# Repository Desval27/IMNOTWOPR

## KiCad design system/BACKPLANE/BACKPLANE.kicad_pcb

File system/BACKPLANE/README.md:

# BACKPLANE

System Bus

Status: Untested

The BACKPLANE PCB provides the shared bus and power distribution for the IMNOTWOPR modular computer, connecting CPU, memory, I/O, and front-panel cards through 20 96-pin DIN 41612 slots. It carries the 24-bit address bus, 8-bit data bus, clock and control signals, and auxiliary I²C and SPI interfaces. ATX power connectors supply the system power rails, with standby power and power-control signals available to the cards. ~~The passive design also includes jumper-selectable I²C pull-ups.~~

~~The PWR module and the BACKPLANE both provide the option for I²C pull-ups for convenience.  Only on should be enabled at a time.~~

Optional I²C pullups will ultimately be provided by the [bus terminator card](../../modules/XXX/README.md).  Support is retained here for testing/hacking purposes and may be removed in a later revision.

## Documents

- [Schematic](BACKPLANE_schematic.pdf)
- [Assembly](BACKPLANE_assembly.pdf)
- [Bill of Materials](bom.csv)
- [Interactive Bill of Materials](ibom.html)

## Gerber To Order

- [Default](gerber_to_order/BACKPLANE_425.28x128.7mm_for_Default.zip)
- [Elecrow](gerber_to_order/BACKPLANE_425.28x128.7mm_for_Elecrow.zip)
- [FusionPCB](gerber_to_order/BACKPLANE_425.28x128.7mm_for_FusionPCB.zip)
- [JLCPCB](gerber_to_order/BACKPLANE_425.28x128.7mm_for_JLCPCB.zip)
- [PCBWay](gerber_to_order/BACKPLANE_425.28x128.7mm_for_PCBWay.zip)

## Rendered Images

### Top 3D

 3D

### Top

### Bottom

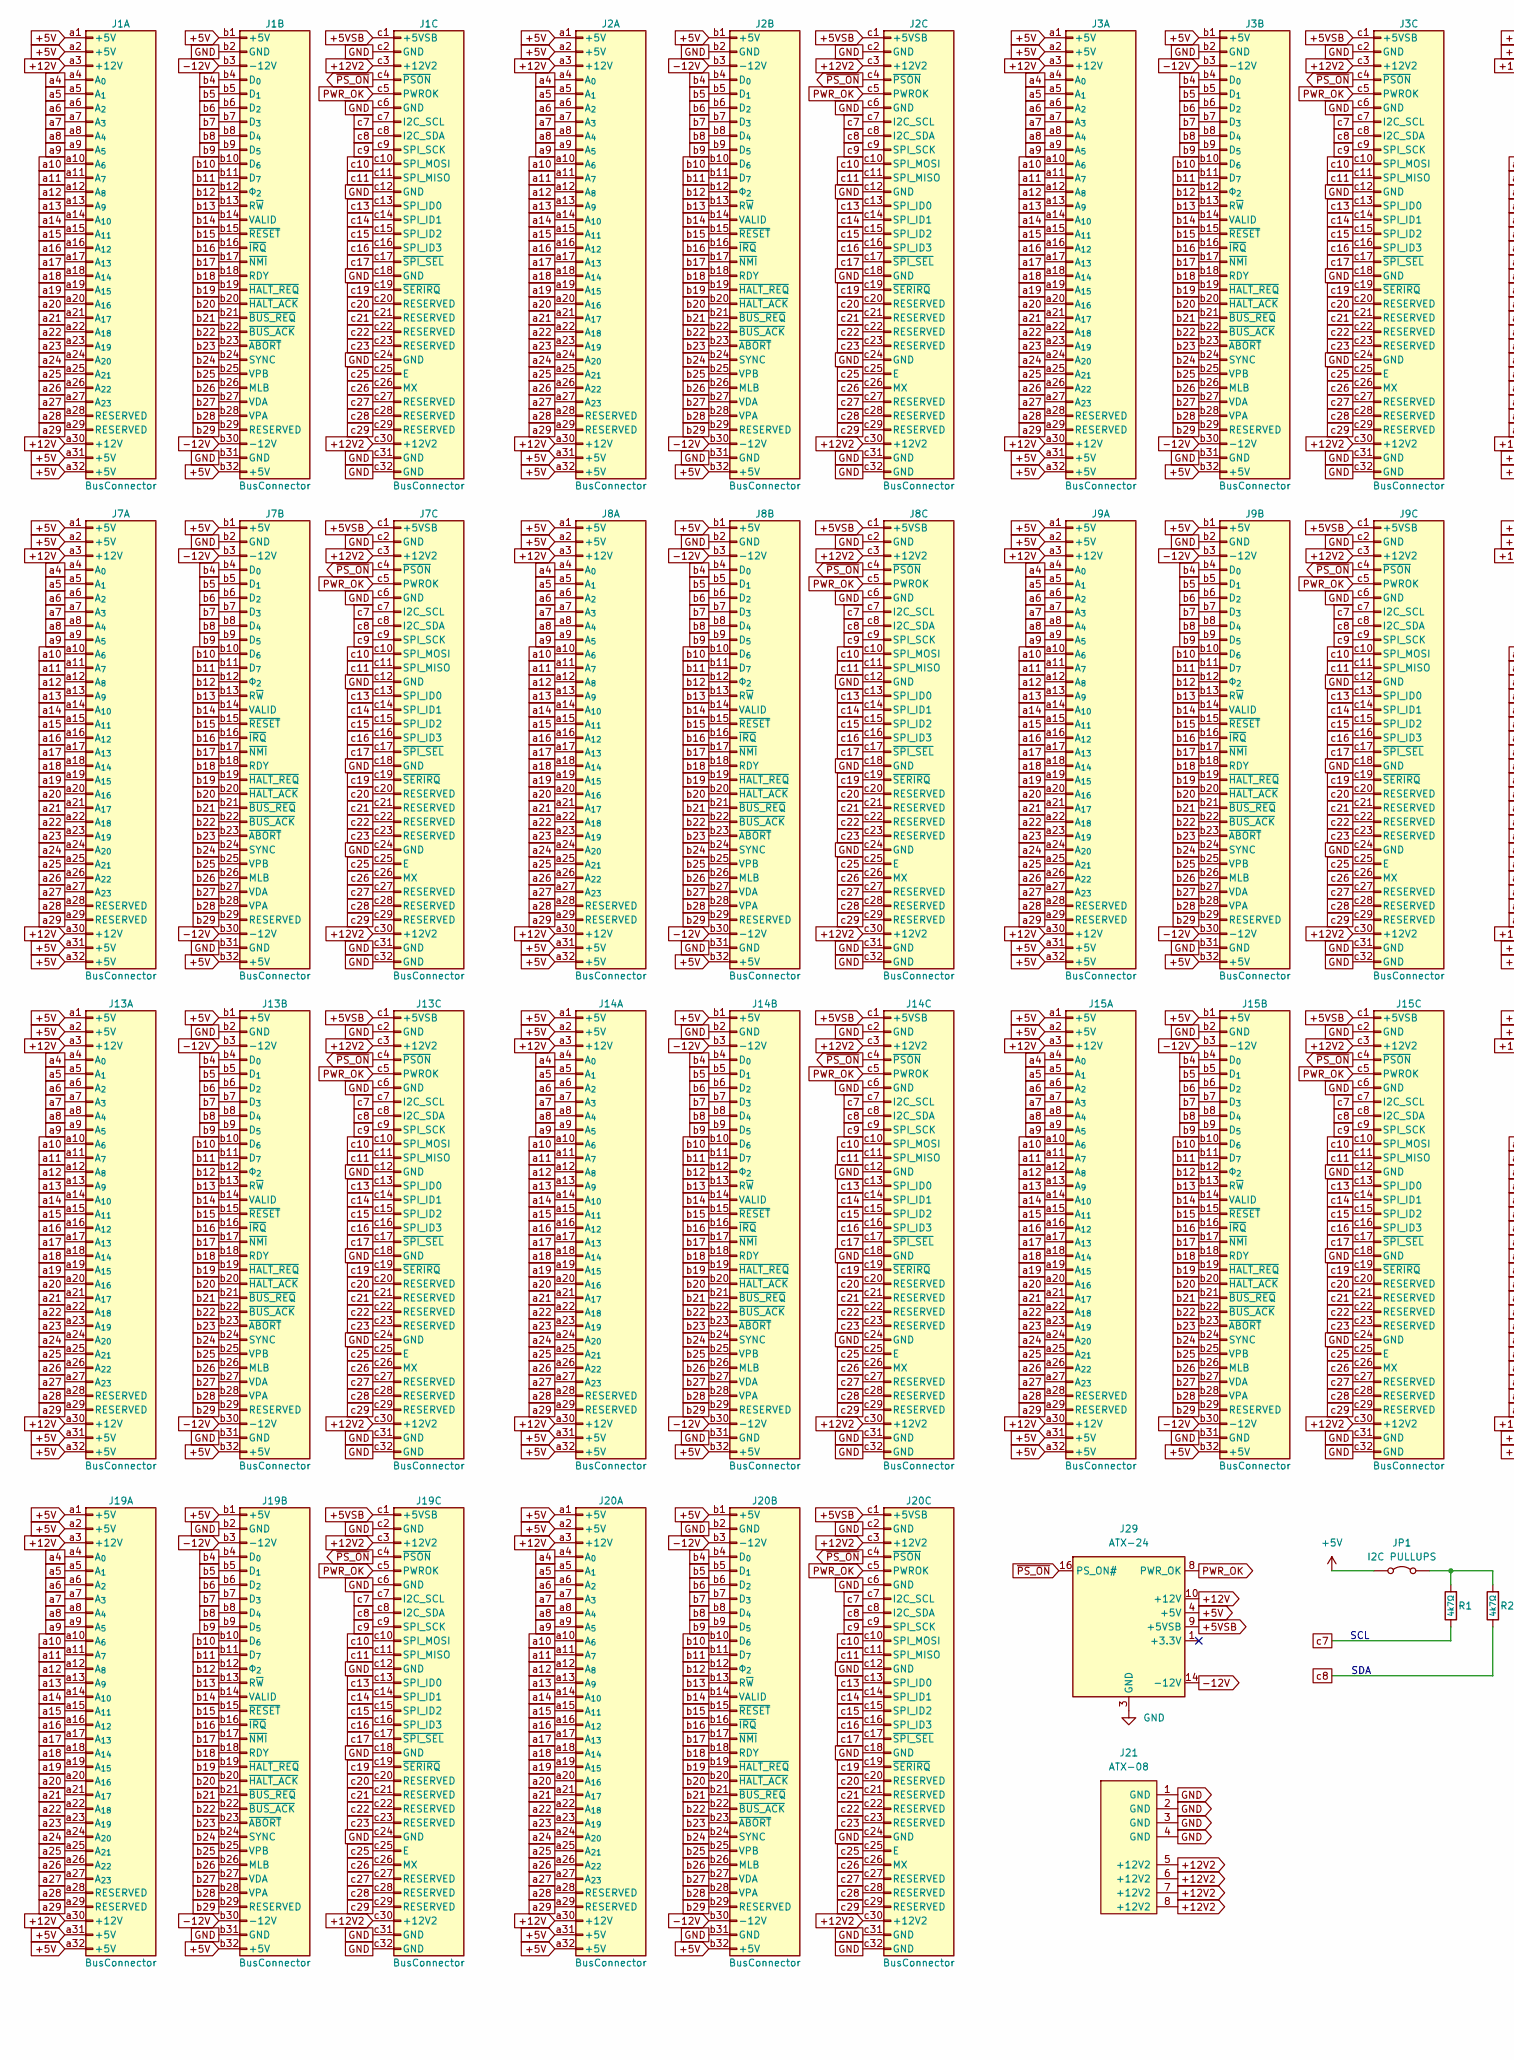
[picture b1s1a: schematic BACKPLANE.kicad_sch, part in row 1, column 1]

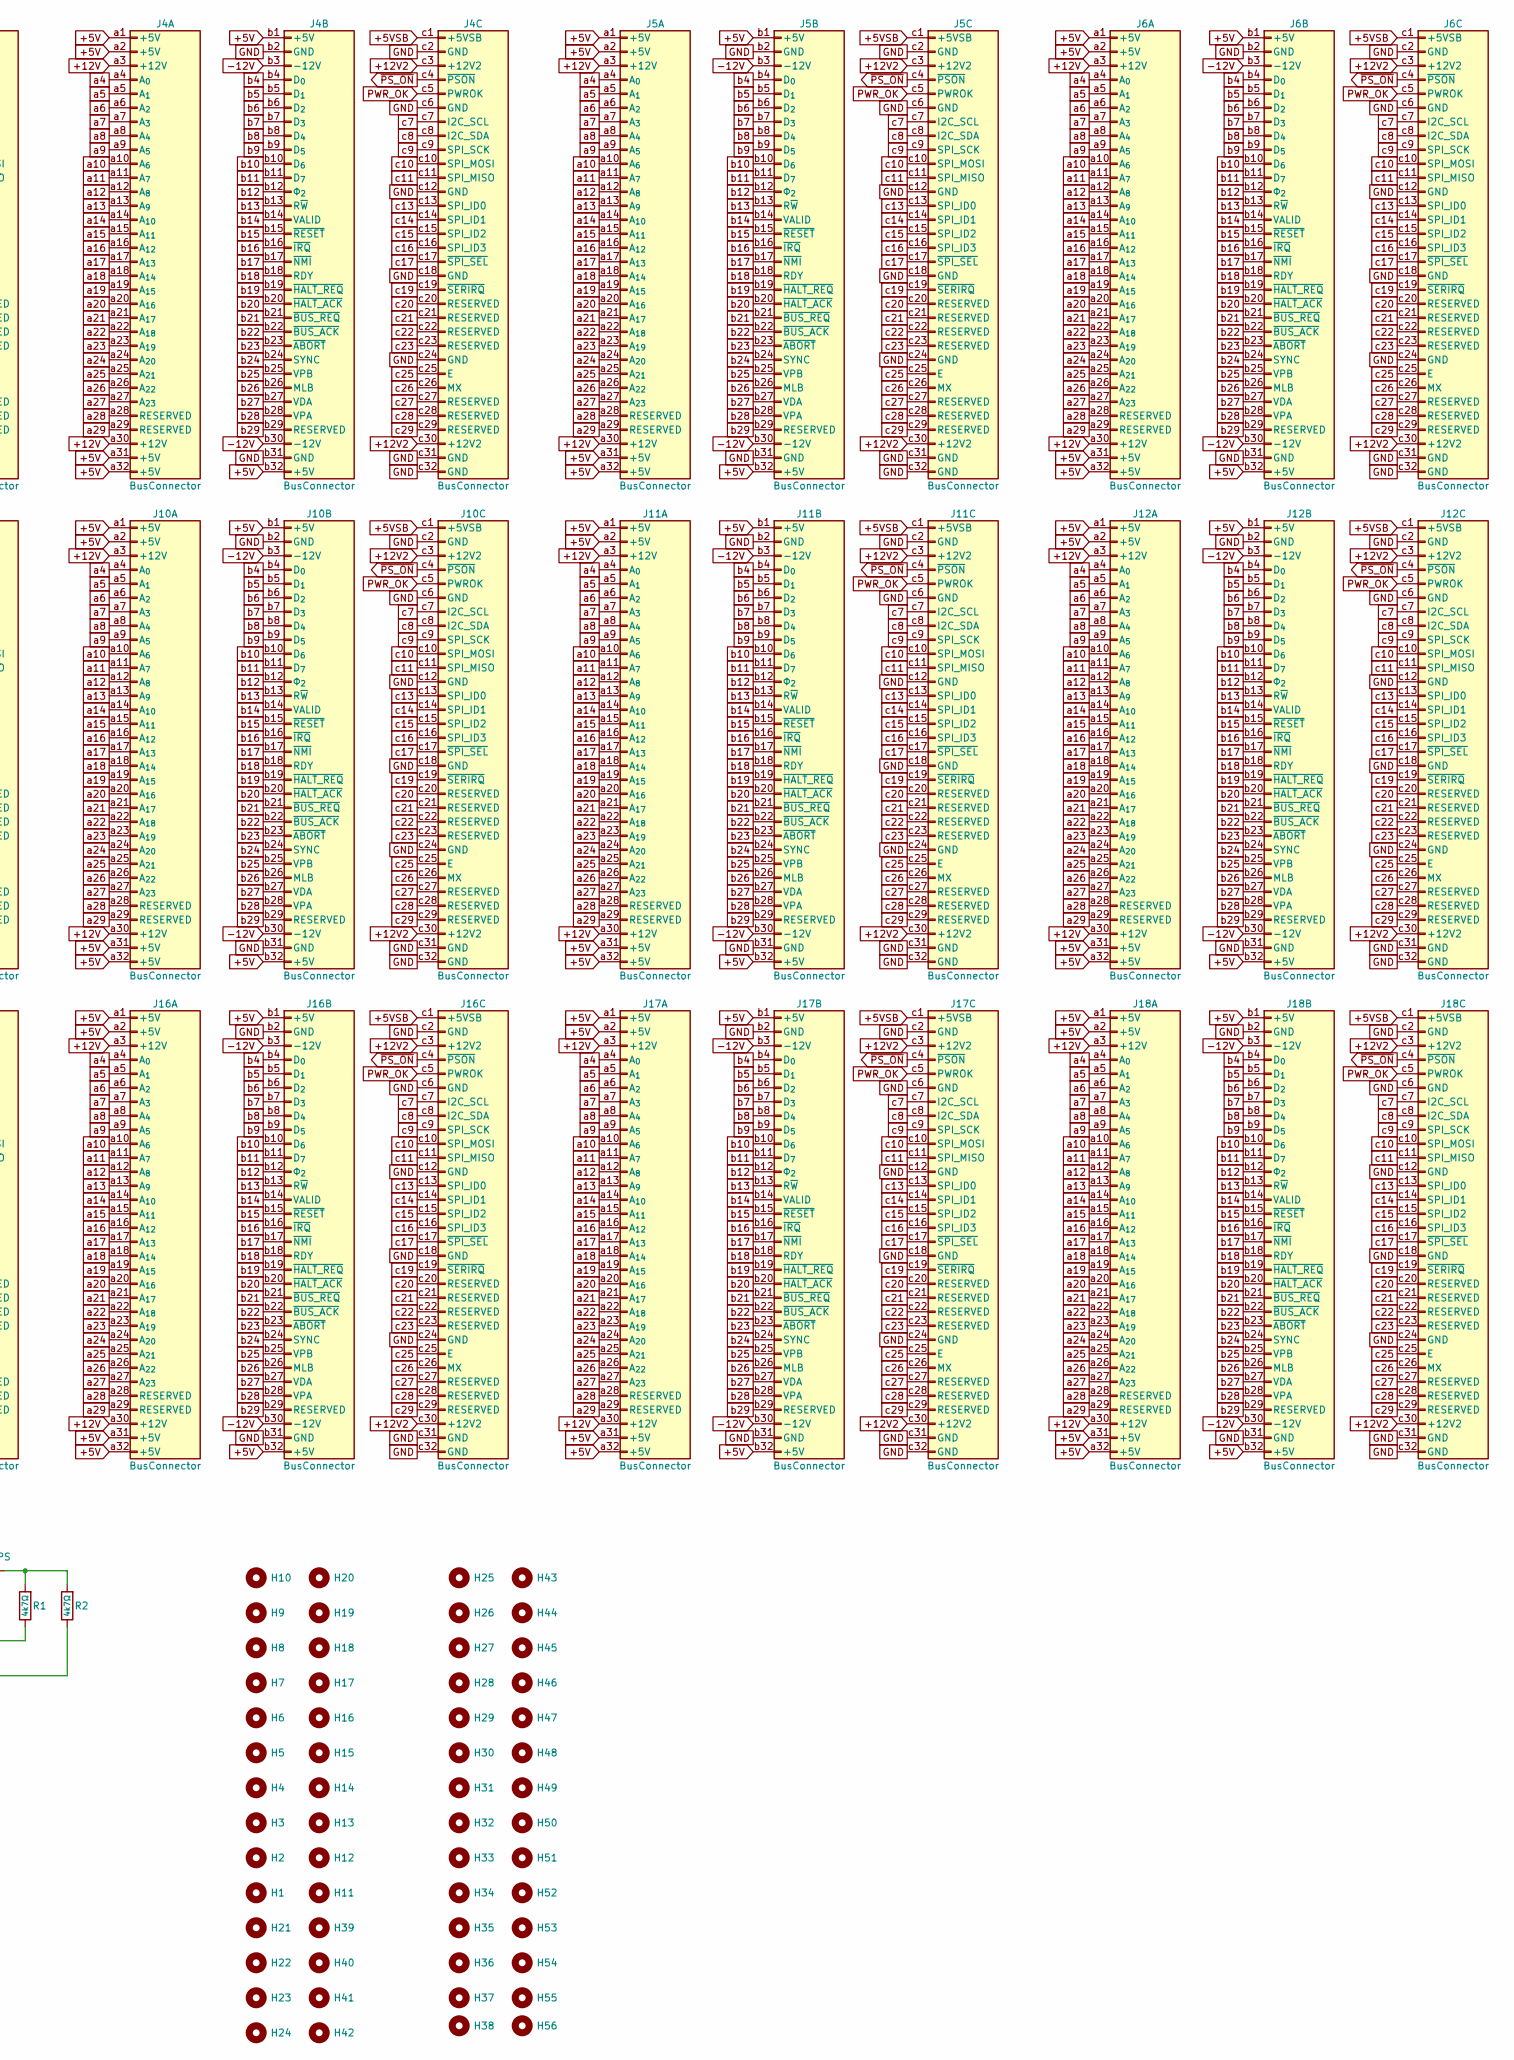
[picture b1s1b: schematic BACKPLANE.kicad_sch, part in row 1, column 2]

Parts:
H1, H2, H3, H4, H5, H6, H7, H8, H9, H10, H11, H12, H13, H14, H15, H16, H17, H18, H19, H20, H21, H22, H23, H24, H25, H26, H27, H28, H29, H30, H31, H32, H33, H34, H35, H36, H37, H38, H39, H40, H41, H42, H43, H44, H45, H46, H47, H48, H49, H50, H51, H52, H53, H54, H55, H56: MountingHole; MountingHole_2.7mm_M2.5
J1, J2, J3, J4, J5, J6, J7, J8, J9, J10, J11, J12, J13, J14, J15, J16, J17, J18, J19, J20: BusConnector; SystemConnector_Female
J21: ATX-08
J29: ATX-24
JP1: I2C PULLUPS; Jumper_1x02
R1, R2: 4k7Ω; R_Axial_DIN0207_P400mil

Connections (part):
+5V: J1.a1 (+5V), J1.a2 (+5V), J1.a31 (+5V), J1.a32 (+5V), J1.b1 (+5V), J1.b32 (+5V), J2.a1 (+5V), J2.a2 (+5V), J2.a31 (+5V), J2.a32 (+5V), J2.b1 (+5V), J2.b32 (+5V), J3.a1 (+5V), J3.a2 (+5V), J3.a31 (+5V), J3.a32 (+5V), J3.b1 (+5V), J3.b32 (+5V), J4.a1 (+5V), J4.a2 (+5V), J4.a31 (+5V), J4.a32 (+5V), J4.b1 (+5V), J4.b32 (+5V), J5.a1 (+5V), J5.a2 (+5V), J5.a31 (+5V), J5.a32 (+5V), J5.b1 (+5V), J5.b32 (+5V), J6.a1 (+5V), J6.a2 (+5V), J6.a31 (+5V), J6.a32 (+5V), J6.b1 (+5V), J6.b32 (+5V), J7.a1 (+5V), J7.a2 (+5V), J7.a31 (+5V), J7.a32 (+5V), J7.b1 (+5V), J7.b32 (+5V), J8.a1 (+5V), J8.a2 (+5V), J8.a31 (+5V), J8.a32 (+5V), J8.b1 (+5V), J8.b32 (+5V), J9.a1 (+5V), J9.a2 (+5V), J9.a31 (+5V), J9.a32 (+5V), J9.b1 (+5V), J9.b32 (+5V), J10.a1 (+5V), J10.a2 (+5V), J10.a31 (+5V), J10.a32 (+5V), J10.b1 (+5V), J10.b32 (+5V), J11.a1 (+5V), J11.a2 (+5V), J11.a31 (+5V), J11.a32 (+5V), J11.b1 (+5V), J11.b32 (+5V), J12.a1 (+5V), J12.a2 (+5V), J12.a31 (+5V), J12.a32 (+5V), J12.b1 (+5V), J12.b32 (+5V), J13.a1 (+5V), J13.a2 (+5V), J13.a31 (+5V), J13.a32 (+5V), J13.b1 (+5V), J13.b32 (+5V), J14.a1 (+5V), J14.a2 (+5V)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
+5VSB: J1.c1 (+5VSB), J2.c1 (+5VSB), J3.c1 (+5VSB), J4.c1 (+5VSB), J5.c1 (+5VSB), J6.c1 (+5VSB), J7.c1 (+5VSB), J8.c1 (+5VSB), J9.c1 (+5VSB), J10.c1 (+5VSB), J11.c1 (+5VSB), J12.c1 (+5VSB), J13.c1 (+5VSB), J14.c1 (+5VSB), J15.c1 (+5VSB), J16.c1 (+5VSB), J17.c1 (+5VSB), J18.c1 (+5VSB), J19.c1 (+5VSB), J20.c1 (+5VSB), J29.9 (+5VSB)
+12V: J1.a3 (+12V), J1.a30 (+12V), J2.a3 (+12V), J2.a30 (+12V), J3.a3 (+12V), J3.a30 (+12V), J4.a3 (+12V), J4.a30 (+12V), J5.a3 (+12V), J5.a30 (+12V), J6.a3 (+12V), J6.a30 (+12V), J7.a3 (+12V), J7.a30 (+12V), J8.a3 (+12V), J8.a30 (+12V), J9.a3 (+12V), J9.a30 (+12V), J10.a3 (+12V), J10.a30 (+12V), J11.a3 (+12V), J11.a30 (+12V), J12.a3 (+12V), J12.a30 (+12V), J13.a3 (+12V), J13.a30 (+12V), J14.a3 (+12V), J14.a30 (+12V), J15.a3 (+12V), J15.a30 (+12V), J16.a3 (+12V), J16.a30 (+12V), J17.a3 (+12V), J17.a30 (+12V), J18.a3 (+12V), J18.a30 (+12V), J19.a3 (+12V), J19.a30 (+12V), J20.a3 (+12V), J20.a30 (+12V), J29.10 (+12V), J29.11 (+12V)
+12V2: J1.c3 (+12V2), J1.c30 (+12V2), J2.c3 (+12V2), J2.c30 (+12V2), J3.c3 (+12V2), J3.c30 (+12V2), J4.c3 (+12V2), J4.c30 (+12V2), J5.c3 (+12V2), J5.c30 (+12V2), J6.c3 (+12V2), J6.c30 (+12V2), J7.c3 (+12V2), J7.c30 (+12V2), J8.c3 (+12V2), J8.c30 (+12V2), J9.c3 (+12V2), J9.c30 (+12V2), J10.c3 (+12V2), J10.c30 (+12V2), J11.c3 (+12V2), J11.c30 (+12V2), J12.c3 (+12V2), J12.c30 (+12V2), J13.c3 (+12V2), J13.c30 (+12V2), J14.c3 (+12V2), J14.c30 (+12V2), J15.c3 (+12V2), J15.c30 (+12V2), J16.c3 (+12V2), J16.c30 (+12V2), J17.c3 (+12V2), J17.c30 (+12V2), J18.c3 (+12V2), J18.c30 (+12V2), J19.c3 (+12V2), J19.c30 (+12V2), J20.c3 (+12V2), J20.c30 (+12V2), J21.5 (+12V2), J21.6 (+12V2), J21.7 (+12V2), J21.8 (+12V2)
-12V: J1.b3 (-12V), J1.b30 (-12V), J2.b3 (-12V), J2.b30 (-12V), J3.b3 (-12V), J3.b30 (-12V), J4.b3 (-12V), J4.b30 (-12V), J5.b3 (-12V), J5.b30 (-12V), J6.b3 (-12V), J6.b30 (-12V), J7.b3 (-12V), J7.b30 (-12V), J8.b3 (-12V), J8.b30 (-12V), J9.b3 (-12V), J9.b30 (-12V), J10.b3 (-12V), J10.b30 (-12V), J11.b3 (-12V), J11.b30 (-12V), J12.b3 (-12V), J12.b30 (-12V), J13.b3 (-12V), J13.b30 (-12V), J14.b3 (-12V), J14.b30 (-12V), J15.b3 (-12V), J15.b30 (-12V), J16.b3 (-12V), J16.b30 (-12V), J17.b3 (-12V), J17.b30 (-12V), J18.b3 (-12V), J18.b30 (-12V), J19.b3 (-12V), J19.b30 (-12V), J20.b3 (-12V), J20.b30 (-12V), J29.14 (-12V)
GND: J1.b2 (GND), J1.b31 (GND), J1.c2 (GND), J1.c6 (GND), J1.c12 (GND), J1.c18 (GND), J1.c24 (GND), J1.c31 (GND), J1.c32 (GND), J2.b2 (GND), J2.b31 (GND), J2.c2 (GND), J2.c6 (GND), J2.c12 (GND), J2.c18 (GND), J2.c24 (GND), J2.c31 (GND), J2.c32 (GND), J3.b2 (GND), J3.b31 (GND), J3.c2 (GND), J3.c6 (GND), J3.c12 (GND), J3.c18 (GND), J3.c24 (GND), J3.c31 (GND), J3.c32 (GND), J4.b2 (GND), J4.b31 (GND), J4.c2 (GND), J4.c6 (GND), J4.c12 (GND), J4.c18 (GND), J4.c24 (GND), J4.c31 (GND), J4.c32 (GND), J5.b2 (GND), J5.b31 (GND), J5.c2 (GND), J5.c6 (GND), J5.c12 (GND), J5.c18 (GND), J5.c24 (GND), J5.c31 (GND), J5.c32 (GND), J6.b2 (GND), J6.b31 (GND), J6.c2 (GND), J6.c6 (GND), J6.c12 (GND), J6.c18 (GND), J6.c24 (GND), J6.c31 (GND), J6.c32 (GND), J7.b2 (GND), J7.b31 (GND), J7.c2 (GND), J7.c6 (GND), J7.c12 (GND), J7.c18 (GND), J7.c24 (GND), J7.c31 (GND), J7.c32 (GND), J8.b2 (GND), J8.b31 (GND), J8.c2 (GND), J8.c6 (GND), J8.c12 (GND), J8.c18 (GND), J8.c24 (GND), J8.c31 (GND), J8.c32 (GND), J9.b2 (GND), J9.b31 (GND), J9.c2 (GND), J9.c6 (GND), J9.c12 (GND), J9.c18 (GND), J9.c24 (GND), J9.c31 (GND)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
unnamed: JP1.2 (B), R1.2, R2.2
PWR_OK: J1.c5 (PWROK), J2.c5 (PWROK), J3.c5 (PWROK), J4.c5 (PWROK), J5.c5 (PWROK), J6.c5 (PWROK), J7.c5 (PWROK), J8.c5 (PWROK), J9.c5 (PWROK), J10.c5 (PWROK), J11.c5 (PWROK), J12.c5 (PWROK), J13.c5 (PWROK), J14.c5 (PWROK), J15.c5 (PWROK), J16.c5 (PWROK), J17.c5 (PWROK), J18.c5 (PWROK), J19.c5 (PWROK), J20.c5 (PWROK), J29.8 (PWR_OK)
a4: J1.a4 (A_{0}), J2.a4 (A_{0}), J3.a4 (A_{0}), J4.a4 (A_{0}), J5.a4 (A_{0}), J6.a4 (A_{0}), J7.a4 (A_{0}), J8.a4 (A_{0}), J9.a4 (A_{0}), J10.a4 (A_{0}), J11.a4 (A_{0}), J12.a4 (A_{0}), J13.a4 (A_{0}), J14.a4 (A_{0}), J15.a4 (A_{0}), J16.a4 (A_{0}), J17.a4 (A_{0}), J18.a4 (A_{0}), J19.a4 (A_{0}), J20.a4 (A_{0})
a5: J1.a5 (A_{1}), J2.a5 (A_{1}), J3.a5 (A_{1}), J4.a5 (A_{1}), J5.a5 (A_{1}), J6.a5 (A_{1}), J7.a5 (A_{1}), J8.a5 (A_{1}), J9.a5 (A_{1}), J10.a5 (A_{1}), J11.a5 (A_{1}), J12.a5 (A_{1}), J13.a5 (A_{1}), J14.a5 (A_{1}), J15.a5 (A_{1}), J16.a5 (A_{1}), J17.a5 (A_{1}), J18.a5 (A_{1}), J19.a5 (A_{1}), J20.a5 (A_{1})
a6: J1.a6 (A_{2}), J2.a6 (A_{2}), J3.a6 (A_{2}), J4.a6 (A_{2}), J5.a6 (A_{2}), J6.a6 (A_{2}), J7.a6 (A_{2}), J8.a6 (A_{2}), J9.a6 (A_{2}), J10.a6 (A_{2}), J11.a6 (A_{2}), J12.a6 (A_{2}), J13.a6 (A_{2}), J14.a6 (A_{2}), J15.a6 (A_{2}), J16.a6 (A_{2}), J17.a6 (A_{2}), J18.a6 (A_{2}), J19.a6 (A_{2}), J20.a6 (A_{2})
a7: J1.a7 (A_{3}), J2.a7 (A_{3}), J3.a7 (A_{3}), J4.a7 (A_{3}), J5.a7 (A_{3}), J6.a7 (A_{3}), J7.a7 (A_{3}), J8.a7 (A_{3}), J9.a7 (A_{3}), J10.a7 (A_{3}), J11.a7 (A_{3}), J12.a7 (A_{3}), J13.a7 (A_{3}), J14.a7 (A_{3}), J15.a7 (A_{3}), J16.a7 (A_{3}), J17.a7 (A_{3}), J18.a7 (A_{3}), J19.a7 (A_{3}), J20.a7 (A_{3})
a8: J1.a8 (A_{4}), J2.a8 (A_{4}), J3.a8 (A_{4}), J4.a8 (A_{4}), J5.a8 (A_{4}), J6.a8 (A_{4}), J7.a8 (A_{4}), J8.a8 (A_{4}), J9.a8 (A_{4}), J10.a8 (A_{4}), J11.a8 (A_{4}), J12.a8 (A_{4}), J13.a8 (A_{4}), J14.a8 (A_{4}), J15.a8 (A_{4}), J16.a8 (A_{4}), J17.a8 (A_{4}), J18.a8 (A_{4}), J19.a8 (A_{4}), J20.a8 (A_{4})
a9: J1.a9 (A_{5}), J2.a9 (A_{5}), J3.a9 (A_{5}), J4.a9 (A_{5}), J5.a9 (A_{5}), J6.a9 (A_{5}), J7.a9 (A_{5}), J8.a9 (A_{5}), J9.a9 (A_{5}), J10.a9 (A_{5}), J11.a9 (A_{5}), J12.a9 (A_{5}), J13.a9 (A_{5}), J14.a9 (A_{5}), J15.a9 (A_{5}), J16.a9 (A_{5}), J17.a9 (A_{5}), J18.a9 (A_{5}), J19.a9 (A_{5}), J20.a9 (A_{5})
a10: J1.a10 (A_{6}), J2.a10 (A_{6}), J3.a10 (A_{6}), J4.a10 (A_{6}), J5.a10 (A_{6}), J6.a10 (A_{6}), J7.a10 (A_{6}), J8.a10 (A_{6}), J9.a10 (A_{6}), J10.a10 (A_{6}), J11.a10 (A_{6}), J12.a10 (A_{6}), J13.a10 (A_{6}), J14.a10 (A_{6}), J15.a10 (A_{6}), J16.a10 (A_{6}), J17.a10 (A_{6}), J18.a10 (A_{6}), J19.a10 (A_{6}), J20.a10 (A_{6})
a11: J1.a11 (A_{7}), J2.a11 (A_{7}), J3.a11 (A_{7}), J4.a11 (A_{7}), J5.a11 (A_{7}), J6.a11 (A_{7}), J7.a11 (A_{7}), J8.a11 (A_{7}), J9.a11 (A_{7}), J10.a11 (A_{7}), J11.a11 (A_{7}), J12.a11 (A_{7}), J13.a11 (A_{7}), J14.a11 (A_{7}), J15.a11 (A_{7}), J16.a11 (A_{7}), J17.a11 (A_{7}), J18.a11 (A_{7}), J19.a11 (A_{7}), J20.a11 (A_{7})
a12: J1.a12 (A_{8}), J2.a12 (A_{8}), J3.a12 (A_{8}), J4.a12 (A_{8}), J5.a12 (A_{8}), J6.a12 (A_{8}), J7.a12 (A_{8}), J8.a12 (A_{8}), J9.a12 (A_{8}), J10.a12 (A_{8}), J11.a12 (A_{8}), J12.a12 (A_{8}), J13.a12 (A_{8}), J14.a12 (A_{8}), J15.a12 (A_{8}), J16.a12 (A_{8}), J17.a12 (A_{8}), J18.a12 (A_{8}), J19.a12 (A_{8}), J20.a12 (A_{8})
a13: J1.a13 (A_{9}), J2.a13 (A_{9}), J3.a13 (A_{9}), J4.a13 (A_{9}), J5.a13 (A_{9}), J6.a13 (A_{9}), J7.a13 (A_{9}), J8.a13 (A_{9}), J9.a13 (A_{9}), J10.a13 (A_{9}), J11.a13 (A_{9}), J12.a13 (A_{9}), J13.a13 (A_{9}), J14.a13 (A_{9}), J15.a13 (A_{9}), J16.a13 (A_{9}), J17.a13 (A_{9}), J18.a13 (A_{9}), J19.a13 (A_{9}), J20.a13 (A_{9})
a14: J1.a14 (A_{10}), J2.a14 (A_{10}), J3.a14 (A_{10}), J4.a14 (A_{10}), J5.a14 (A_{10}), J6.a14 (A_{10}), J7.a14 (A_{10}), J8.a14 (A_{10}), J9.a14 (A_{10}), J10.a14 (A_{10}), J11.a14 (A_{10}), J12.a14 (A_{10}), J13.a14 (A_{10}), J14.a14 (A_{10}), J15.a14 (A_{10}), J16.a14 (A_{10}), J17.a14 (A_{10}), J18.a14 (A_{10}), J19.a14 (A_{10}), J20.a14 (A_{10})
a15: J1.a15 (A_{11}), J2.a15 (A_{11}), J3.a15 (A_{11}), J4.a15 (A_{11}), J5.a15 (A_{11}), J6.a15 (A_{11}), J7.a15 (A_{11}), J8.a15 (A_{11}), J9.a15 (A_{11}), J10.a15 (A_{11}), J11.a15 (A_{11}), J12.a15 (A_{11}), J13.a15 (A_{11}), J14.a15 (A_{11}), J15.a15 (A_{11}), J16.a15 (A_{11}), J17.a15 (A_{11}), J18.a15 (A_{11}), J19.a15 (A_{11}), J20.a15 (A_{11})
a16: J1.a16 (A_{12}), J2.a16 (A_{12}), J3.a16 (A_{12}), J4.a16 (A_{12}), J5.a16 (A_{12}), J6.a16 (A_{12}), J7.a16 (A_{12}), J8.a16 (A_{12}), J9.a16 (A_{12}), J10.a16 (A_{12}), J11.a16 (A_{12}), J12.a16 (A_{12}), J13.a16 (A_{12}), J14.a16 (A_{12}), J15.a16 (A_{12}), J16.a16 (A_{12}), J17.a16 (A_{12}), J18.a16 (A_{12}), J19.a16 (A_{12}), J20.a16 (A_{12})
a17: J1.a17 (A_{13}), J2.a17 (A_{13}), J3.a17 (A_{13}), J4.a17 (A_{13}), J5.a17 (A_{13}), J6.a17 (A_{13}), J7.a17 (A_{13}), J8.a17 (A_{13}), J9.a17 (A_{13}), J10.a17 (A_{13}), J11.a17 (A_{13}), J12.a17 (A_{13}), J13.a17 (A_{13}), J14.a17 (A_{13}), J15.a17 (A_{13}), J16.a17 (A_{13}), J17.a17 (A_{13}), J18.a17 (A_{13}), J19.a17 (A_{13}), J20.a17 (A_{13})
a18: J1.a18 (A_{14}), J2.a18 (A_{14}), J3.a18 (A_{14}), J4.a18 (A_{14}), J5.a18 (A_{14}), J6.a18 (A_{14}), J7.a18 (A_{14}), J8.a18 (A_{14}), J9.a18 (A_{14}), J10.a18 (A_{14}), J11.a18 (A_{14}), J12.a18 (A_{14}), J13.a18 (A_{14}), J14.a18 (A_{14}), J15.a18 (A_{14}), J16.a18 (A_{14}), J17.a18 (A_{14}), J18.a18 (A_{14}), J19.a18 (A_{14}), J20.a18 (A_{14})
a19: J1.a19 (A_{15}), J2.a19 (A_{15}), J3.a19 (A_{15}), J4.a19 (A_{15}), J5.a19 (A_{15}), J6.a19 (A_{15}), J7.a19 (A_{15}), J8.a19 (A_{15}), J9.a19 (A_{15}), J10.a19 (A_{15}), J11.a19 (A_{15}), J12.a19 (A_{15}), J13.a19 (A_{15}), J14.a19 (A_{15}), J15.a19 (A_{15}), J16.a19 (A_{15}), J17.a19 (A_{15}), J18.a19 (A_{15}), J19.a19 (A_{15}), J20.a19 (A_{15})
a20: J1.a20 (A_{16}), J2.a20 (A_{16}), J3.a20 (A_{16}), J4.a20 (A_{16}), J5.a20 (A_{16}), J6.a20 (A_{16}), J7.a20 (A_{16}), J8.a20 (A_{16}), J9.a20 (A_{16}), J10.a20 (A_{16}), J11.a20 (A_{16}), J12.a20 (A_{16}), J13.a20 (A_{16}), J14.a20 (A_{16}), J15.a20 (A_{16}), J16.a20 (A_{16}), J17.a20 (A_{16}), J18.a20 (A_{16}), J19.a20 (A_{16}), J20.a20 (A_{16})
a21: J1.a21 (A_{17}), J2.a21 (A_{17}), J3.a21 (A_{17}), J4.a21 (A_{17}), J5.a21 (A_{17}), J6.a21 (A_{17}), J7.a21 (A_{17}), J8.a21 (A_{17}), J9.a21 (A_{17}), J10.a21 (A_{17}), J11.a21 (A_{17}), J12.a21 (A_{17}), J13.a21 (A_{17}), J14.a21 (A_{17}), J15.a21 (A_{17}), J16.a21 (A_{17}), J17.a21 (A_{17}), J18.a21 (A_{17}), J19.a21 (A_{17}), J20.a21 (A_{17})
a22: J1.a22 (A_{18}), J2.a22 (A_{18}), J3.a22 (A_{18}), J4.a22 (A_{18}), J5.a22 (A_{18}), J6.a22 (A_{18}), J7.a22 (A_{18}), J8.a22 (A_{18}), J9.a22 (A_{18}), J10.a22 (A_{18}), J11.a22 (A_{18}), J12.a22 (A_{18}), J13.a22 (A_{18}), J14.a22 (A_{18}), J15.a22 (A_{18}), J16.a22 (A_{18}), J17.a22 (A_{18}), J18.a22 (A_{18}), J19.a22 (A_{18}), J20.a22 (A_{18})
a23: J1.a23 (A_{19}), J2.a23 (A_{19}), J3.a23 (A_{19}), J4.a23 (A_{19}), J5.a23 (A_{19}), J6.a23 (A_{19}), J7.a23 (A_{19}), J8.a23 (A_{19}), J9.a23 (A_{19}), J10.a23 (A_{19}), J11.a23 (A_{19}), J12.a23 (A_{19}), J13.a23 (A_{19}), J14.a23 (A_{19}), J15.a23 (A_{19}), J16.a23 (A_{19}), J17.a23 (A_{19}), J18.a23 (A_{19}), J19.a23 (A_{19}), J20.a23 (A_{19})
a24: J1.a24 (A_{20}), J2.a24 (A_{20}), J3.a24 (A_{20}), J4.a24 (A_{20}), J5.a24 (A_{20}), J6.a24 (A_{20}), J7.a24 (A_{20}), J8.a24 (A_{20}), J9.a24 (A_{20}), J10.a24 (A_{20}), J11.a24 (A_{20}), J12.a24 (A_{20}), J13.a24 (A_{20}), J14.a24 (A_{20}), J15.a24 (A_{20}), J16.a24 (A_{20}), J17.a24 (A_{20}), J18.a24 (A_{20}), J19.a24 (A_{20}), J20.a24 (A_{20})
a25: J1.a25 (A_{21}), J2.a25 (A_{21}), J3.a25 (A_{21}), J4.a25 (A_{21}), J5.a25 (A_{21}), J6.a25 (A_{21}), J7.a25 (A_{21}), J8.a25 (A_{21}), J9.a25 (A_{21}), J10.a25 (A_{21}), J11.a25 (A_{21}), J12.a25 (A_{21}), J13.a25 (A_{21}), J14.a25 (A_{21}), J15.a25 (A_{21}), J16.a25 (A_{21}), J17.a25 (A_{21}), J18.a25 (A_{21}), J19.a25 (A_{21}), J20.a25 (A_{21})
a26: J1.a26 (A_{22}), J2.a26 (A_{22}), J3.a26 (A_{22}), J4.a26 (A_{22}), J5.a26 (A_{22}), J6.a26 (A_{22}), J7.a26 (A_{22}), J8.a26 (A_{22}), J9.a26 (A_{22}), J10.a26 (A_{22}), J11.a26 (A_{22}), J12.a26 (A_{22}), J13.a26 (A_{22}), J14.a26 (A_{22}), J15.a26 (A_{22}), J16.a26 (A_{22}), J17.a26 (A_{22}), J18.a26 (A_{22}), J19.a26 (A_{22}), J20.a26 (A_{22})
a27: J1.a27 (A_{23}), J2.a27 (A_{23}), J3.a27 (A_{23}), J4.a27 (A_{23}), J5.a27 (A_{23}), J6.a27 (A_{23}), J7.a27 (A_{23}), J8.a27 (A_{23}), J9.a27 (A_{23}), J10.a27 (A_{23}), J11.a27 (A_{23}), J12.a27 (A_{23}), J13.a27 (A_{23}), J14.a27 (A_{23}), J15.a27 (A_{23}), J16.a27 (A_{23}), J17.a27 (A_{23}), J18.a27 (A_{23}), J19.a27 (A_{23}), J20.a27 (A_{23})
a28: J1.a28 (RESERVED), J2.a28 (RESERVED), J3.a28 (RESERVED), J4.a28 (RESERVED), J5.a28 (RESERVED), J6.a28 (RESERVED), J7.a28 (RESERVED), J8.a28 (RESERVED), J9.a28 (RESERVED), J10.a28 (RESERVED), J11.a28 (RESERVED), J12.a28 (RESERVED), J13.a28 (RESERVED), J14.a28 (RESERVED), J15.a28 (RESERVED), J16.a28 (RESERVED), J17.a28 (RESERVED), J18.a28 (RESERVED), J19.a28 (RESERVED), J20.a28 (RESERVED)
a29: J1.a29 (RESERVED), J2.a29 (RESERVED), J3.a29 (RESERVED), J4.a29 (RESERVED), J5.a29 (RESERVED), J6.a29 (RESERVED), J7.a29 (RESERVED), J8.a29 (RESERVED), J9.a29 (RESERVED), J10.a29 (RESERVED), J11.a29 (RESERVED), J12.a29 (RESERVED), J13.a29 (RESERVED), J14.a29 (RESERVED), J15.a29 (RESERVED), J16.a29 (RESERVED), J17.a29 (RESERVED), J18.a29 (RESERVED), J19.a29 (RESERVED), J20.a29 (RESERVED)
b4: J1.b4 (D_{0}), J2.b4 (D_{0}), J3.b4 (D_{0}), J4.b4 (D_{0}), J5.b4 (D_{0}), J6.b4 (D_{0}), J7.b4 (D_{0}), J8.b4 (D_{0}), J9.b4 (D_{0}), J10.b4 (D_{0}), J11.b4 (D_{0}), J12.b4 (D_{0}), J13.b4 (D_{0}), J14.b4 (D_{0}), J15.b4 (D_{0}), J16.b4 (D_{0}), J17.b4 (D_{0}), J18.b4 (D_{0}), J19.b4 (D_{0}), J20.b4 (D_{0})
b5: J1.b5 (D_{1}), J2.b5 (D_{1}), J3.b5 (D_{1}), J4.b5 (D_{1}), J5.b5 (D_{1}), J6.b5 (D_{1}), J7.b5 (D_{1}), J8.b5 (D_{1}), J9.b5 (D_{1}), J10.b5 (D_{1}), J11.b5 (D_{1}), J12.b5 (D_{1}), J13.b5 (D_{1}), J14.b5 (D_{1}), J15.b5 (D_{1}), J16.b5 (D_{1}), J17.b5 (D_{1}), J18.b5 (D_{1}), J19.b5 (D_{1}), J20.b5 (D_{1})
b6: J1.b6 (D_{2}), J2.b6 (D_{2}), J3.b6 (D_{2}), J4.b6 (D_{2}), J5.b6 (D_{2}), J6.b6 (D_{2}), J7.b6 (D_{2}), J8.b6 (D_{2}), J9.b6 (D_{2}), J10.b6 (D_{2}), J11.b6 (D_{2}), J12.b6 (D_{2}), J13.b6 (D_{2}), J14.b6 (D_{2}), J15.b6 (D_{2}), J16.b6 (D_{2}), J17.b6 (D_{2}), J18.b6 (D_{2}), J19.b6 (D_{2}), J20.b6 (D_{2})
b7: J1.b7 (D_{3}), J2.b7 (D_{3}), J3.b7 (D_{3}), J4.b7 (D_{3}), J5.b7 (D_{3}), J6.b7 (D_{3}), J7.b7 (D_{3}), J8.b7 (D_{3}), J9.b7 (D_{3}), J10.b7 (D_{3}), J11.b7 (D_{3}), J12.b7 (D_{3}), J13.b7 (D_{3}), J14.b7 (D_{3}), J15.b7 (D_{3}), J16.b7 (D_{3}), J17.b7 (D_{3}), J18.b7 (D_{3}), J19.b7 (D_{3}), J20.b7 (D_{3})
b8: J1.b8 (D_{4}), J2.b8 (D_{4}), J3.b8 (D_{4}), J4.b8 (D_{4}), J5.b8 (D_{4}), J6.b8 (D_{4}), J7.b8 (D_{4}), J8.b8 (D_{4}), J9.b8 (D_{4}), J10.b8 (D_{4}), J11.b8 (D_{4}), J12.b8 (D_{4}), J13.b8 (D_{4}), J14.b8 (D_{4}), J15.b8 (D_{4}), J16.b8 (D_{4}), J17.b8 (D_{4}), J18.b8 (D_{4}), J19.b8 (D_{4}), J20.b8 (D_{4})
b9: J1.b9 (D_{5}), J2.b9 (D_{5}), J3.b9 (D_{5}), J4.b9 (D_{5}), J5.b9 (D_{5}), J6.b9 (D_{5}), J7.b9 (D_{5}), J8.b9 (D_{5}), J9.b9 (D_{5}), J10.b9 (D_{5}), J11.b9 (D_{5}), J12.b9 (D_{5}), J13.b9 (D_{5}), J14.b9 (D_{5}), J15.b9 (D_{5}), J16.b9 (D_{5}), J17.b9 (D_{5}), J18.b9 (D_{5}), J19.b9 (D_{5}), J20.b9 (D_{5})
b10: J1.b10 (D_{6}), J2.b10 (D_{6}), J3.b10 (D_{6}), J4.b10 (D_{6}), J5.b10 (D_{6}), J6.b10 (D_{6}), J7.b10 (D_{6}), J8.b10 (D_{6}), J9.b10 (D_{6}), J10.b10 (D_{6}), J11.b10 (D_{6}), J12.b10 (D_{6}), J13.b10 (D_{6}), J14.b10 (D_{6}), J15.b10 (D_{6}), J16.b10 (D_{6}), J17.b10 (D_{6}), J18.b10 (D_{6}), J19.b10 (D_{6}), J20.b10 (D_{6})
b11: J1.b11 (D_{7}), J2.b11 (D_{7}), J3.b11 (D_{7}), J4.b11 (D_{7}), J5.b11 (D_{7}), J6.b11 (D_{7}), J7.b11 (D_{7}), J8.b11 (D_{7}), J9.b11 (D_{7}), J10.b11 (D_{7}), J11.b11 (D_{7}), J12.b11 (D_{7}), J13.b11 (D_{7}), J14.b11 (D_{7}), J15.b11 (D_{7}), J16.b11 (D_{7}), J17.b11 (D_{7}), J18.b11 (D_{7}), J19.b11 (D_{7}), J20.b11 (D_{7})
b12: J1.b12 (Φ_{2}), J2.b12 (Φ_{2}), J3.b12 (Φ_{2}), J4.b12 (Φ_{2}), J5.b12 (Φ_{2}), J6.b12 (Φ_{2}), J7.b12 (Φ_{2}), J8.b12 (Φ_{2}), J9.b12 (Φ_{2}), J10.b12 (Φ_{2}), J11.b12 (Φ_{2}), J12.b12 (Φ_{2}), J13.b12 (Φ_{2}), J14.b12 (Φ_{2}), J15.b12 (Φ_{2}), J16.b12 (Φ_{2}), J17.b12 (Φ_{2}), J18.b12 (Φ_{2}), J19.b12 (Φ_{2}), J20.b12 (Φ_{2})
b13: J1.b13 (R~W), J2.b13 (R~W), J3.b13 (R~W), J4.b13 (R~W), J5.b13 (R~W), J6.b13 (R~W), J7.b13 (R~W), J8.b13 (R~W), J9.b13 (R~W), J10.b13 (R~W), J11.b13 (R~W), J12.b13 (R~W), J13.b13 (R~W), J14.b13 (R~W), J15.b13 (R~W), J16.b13 (R~W), J17.b13 (R~W), J18.b13 (R~W), J19.b13 (R~W), J20.b13 (R~W)
b14: J1.b14 (VALID), J2.b14 (VALID), J3.b14 (VALID), J4.b14 (VALID), J5.b14 (VALID), J6.b14 (VALID), J7.b14 (VALID), J8.b14 (VALID), J9.b14 (VALID), J10.b14 (VALID), J11.b14 (VALID), J12.b14 (VALID), J13.b14 (VALID), J14.b14 (VALID), J15.b14 (VALID), J16.b14 (VALID), J17.b14 (VALID), J18.b14 (VALID), J19.b14 (VALID), J20.b14 (VALID)
b15: J1.b15 (~RESET), J2.b15 (~RESET), J3.b15 (~RESET), J4.b15 (~RESET), J5.b15 (~RESET), J6.b15 (~RESET), J7.b15 (~RESET), J8.b15 (~RESET), J9.b15 (~RESET), J10.b15 (~RESET), J11.b15 (~RESET), J12.b15 (~RESET), J13.b15 (~RESET), J14.b15 (~RESET), J15.b15 (~RESET), J16.b15 (~RESET), J17.b15 (~RESET), J18.b15 (~RESET), J19.b15 (~RESET), J20.b15 (~RESET)
b16: J1.b16 (~IRQ), J2.b16 (~IRQ), J3.b16 (~IRQ), J4.b16 (~IRQ), J5.b16 (~IRQ), J6.b16 (~IRQ), J7.b16 (~IRQ), J8.b16 (~IRQ), J9.b16 (~IRQ), J10.b16 (~IRQ), J11.b16 (~IRQ), J12.b16 (~IRQ), J13.b16 (~IRQ), J14.b16 (~IRQ), J15.b16 (~IRQ), J16.b16 (~IRQ), J17.b16 (~IRQ), J18.b16 (~IRQ), J19.b16 (~IRQ), J20.b16 (~IRQ)
b17: J1.b17 (~NMI), J2.b17 (~NMI), J3.b17 (~NMI), J4.b17 (~NMI), J5.b17 (~NMI), J6.b17 (~NMI), J7.b17 (~NMI), J8.b17 (~NMI), J9.b17 (~NMI), J10.b17 (~NMI), J11.b17 (~NMI), J12.b17 (~NMI), J13.b17 (~NMI), J14.b17 (~NMI), J15.b17 (~NMI), J16.b17 (~NMI), J17.b17 (~NMI), J18.b17 (~NMI), J19.b17 (~NMI), J20.b17 (~NMI)
b18: J1.b18 (RDY), J2.b18 (RDY), J3.b18 (RDY), J4.b18 (RDY), J5.b18 (RDY), J6.b18 (RDY), J7.b18 (RDY), J8.b18 (RDY), J9.b18 (RDY), J10.b18 (RDY), J11.b18 (RDY), J12.b18 (RDY), J13.b18 (RDY), J14.b18 (RDY), J15.b18 (RDY), J16.b18 (RDY), J17.b18 (RDY), J18.b18 (RDY), J19.b18 (RDY), J20.b18 (RDY)
b19: J1.b19 (~HALT_REQ), J2.b19 (~HALT_REQ), J3.b19 (~HALT_REQ), J4.b19 (~HALT_REQ), J5.b19 (~HALT_REQ), J6.b19 (~HALT_REQ), J7.b19 (~HALT_REQ), J8.b19 (~HALT_REQ), J9.b19 (~HALT_REQ), J10.b19 (~HALT_REQ), J11.b19 (~HALT_REQ), J12.b19 (~HALT_REQ), J13.b19 (~HALT_REQ), J14.b19 (~HALT_REQ), J15.b19 (~HALT_REQ), J16.b19 (~HALT_REQ), J17.b19 (~HALT_REQ), J18.b19 (~HALT_REQ), J19.b19 (~HALT_REQ), J20.b19 (~HALT_REQ)
b20: J1.b20 (~HALT_ACK), J2.b20 (~HALT_ACK), J3.b20 (~HALT_ACK), J4.b20 (~HALT_ACK), J5.b20 (~HALT_ACK), J6.b20 (~HALT_ACK), J7.b20 (~HALT_ACK), J8.b20 (~HALT_ACK), J9.b20 (~HALT_ACK), J10.b20 (~HALT_ACK), J11.b20 (~HALT_ACK), J12.b20 (~HALT_ACK), J13.b20 (~HALT_ACK), J14.b20 (~HALT_ACK), J15.b20 (~HALT_ACK), J16.b20 (~HALT_ACK), J17.b20 (~HALT_ACK), J18.b20 (~HALT_ACK), J19.b20 (~HALT_ACK), J20.b20 (~HALT_ACK)
b21: J1.b21 (~BUS_REQ), J2.b21 (~BUS_REQ), J3.b21 (~BUS_REQ), J4.b21 (~BUS_REQ), J5.b21 (~BUS_REQ), J6.b21 (~BUS_REQ), J7.b21 (~BUS_REQ), J8.b21 (~BUS_REQ), J9.b21 (~BUS_REQ), J10.b21 (~BUS_REQ), J11.b21 (~BUS_REQ), J12.b21 (~BUS_REQ), J13.b21 (~BUS_REQ), J14.b21 (~BUS_REQ), J15.b21 (~BUS_REQ), J16.b21 (~BUS_REQ), J17.b21 (~BUS_REQ), J18.b21 (~BUS_REQ), J19.b21 (~BUS_REQ), J20.b21 (~BUS_REQ)
b22: J1.b22 (~BUS_ACK), J2.b22 (~BUS_ACK), J3.b22 (~BUS_ACK), J4.b22 (~BUS_ACK), J5.b22 (~BUS_ACK), J6.b22 (~BUS_ACK), J7.b22 (~BUS_ACK), J8.b22 (~BUS_ACK), J9.b22 (~BUS_ACK), J10.b22 (~BUS_ACK), J11.b22 (~BUS_ACK), J12.b22 (~BUS_ACK), J13.b22 (~BUS_ACK), J14.b22 (~BUS_ACK), J15.b22 (~BUS_ACK), J16.b22 (~BUS_ACK), J17.b22 (~BUS_ACK), J18.b22 (~BUS_ACK), J19.b22 (~BUS_ACK), J20.b22 (~BUS_ACK)
b23: J1.b23 (~ABORT), J2.b23 (~ABORT), J3.b23 (~ABORT), J4.b23 (~ABORT), J5.b23 (~ABORT), J6.b23 (~ABORT), J7.b23 (~ABORT), J8.b23 (~ABORT), J9.b23 (~ABORT), J10.b23 (~ABORT), J11.b23 (~ABORT), J12.b23 (~ABORT), J13.b23 (~ABORT), J14.b23 (~ABORT), J15.b23 (~ABORT), J16.b23 (~ABORT), J17.b23 (~ABORT), J18.b23 (~ABORT), J19.b23 (~ABORT), J20.b23 (~ABORT)
b24: J1.b24 (SYNC), J2.b24 (SYNC), J3.b24 (SYNC), J4.b24 (SYNC), J5.b24 (SYNC), J6.b24 (SYNC), J7.b24 (SYNC), J8.b24 (SYNC), J9.b24 (SYNC), J10.b24 (SYNC), J11.b24 (SYNC), J12.b24 (SYNC), J13.b24 (SYNC), J14.b24 (SYNC), J15.b24 (SYNC), J16.b24 (SYNC), J17.b24 (SYNC), J18.b24 (SYNC), J19.b24 (SYNC), J20.b24 (SYNC)
b25: J1.b25 (VPB), J2.b25 (VPB), J3.b25 (VPB), J4.b25 (VPB), J5.b25 (VPB), J6.b25 (VPB), J7.b25 (VPB), J8.b25 (VPB), J9.b25 (VPB), J10.b25 (VPB), J11.b25 (VPB), J12.b25 (VPB), J13.b25 (VPB), J14.b25 (VPB), J15.b25 (VPB), J16.b25 (VPB), J17.b25 (VPB), J18.b25 (VPB), J19.b25 (VPB), J20.b25 (VPB)
b26: J1.b26 (MLB), J2.b26 (MLB), J3.b26 (MLB), J4.b26 (MLB), J5.b26 (MLB), J6.b26 (MLB), J7.b26 (MLB), J8.b26 (MLB), J9.b26 (MLB), J10.b26 (MLB), J11.b26 (MLB), J12.b26 (MLB), J13.b26 (MLB), J14.b26 (MLB), J15.b26 (MLB), J16.b26 (MLB), J17.b26 (MLB), J18.b26 (MLB), J19.b26 (MLB), J20.b26 (MLB)
b27: J1.b27 (VDA), J2.b27 (VDA), J3.b27 (VDA), J4.b27 (VDA), J5.b27 (VDA), J6.b27 (VDA), J7.b27 (VDA), J8.b27 (VDA), J9.b27 (VDA), J10.b27 (VDA), J11.b27 (VDA), J12.b27 (VDA), J13.b27 (VDA), J14.b27 (VDA), J15.b27 (VDA), J16.b27 (VDA), J17.b27 (VDA), J18.b27 (VDA), J19.b27 (VDA), J20.b27 (VDA)
b28: J1.b28 (VPA), J2.b28 (VPA), J3.b28 (VPA), J4.b28 (VPA), J5.b28 (VPA), J6.b28 (VPA), J7.b28 (VPA), J8.b28 (VPA), J9.b28 (VPA), J10.b28 (VPA), J11.b28 (VPA), J12.b28 (VPA), J13.b28 (VPA), J14.b28 (VPA), J15.b28 (VPA), J16.b28 (VPA), J17.b28 (VPA), J18.b28 (VPA), J19.b28 (VPA), J20.b28 (VPA)
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
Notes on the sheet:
SCL
SDA

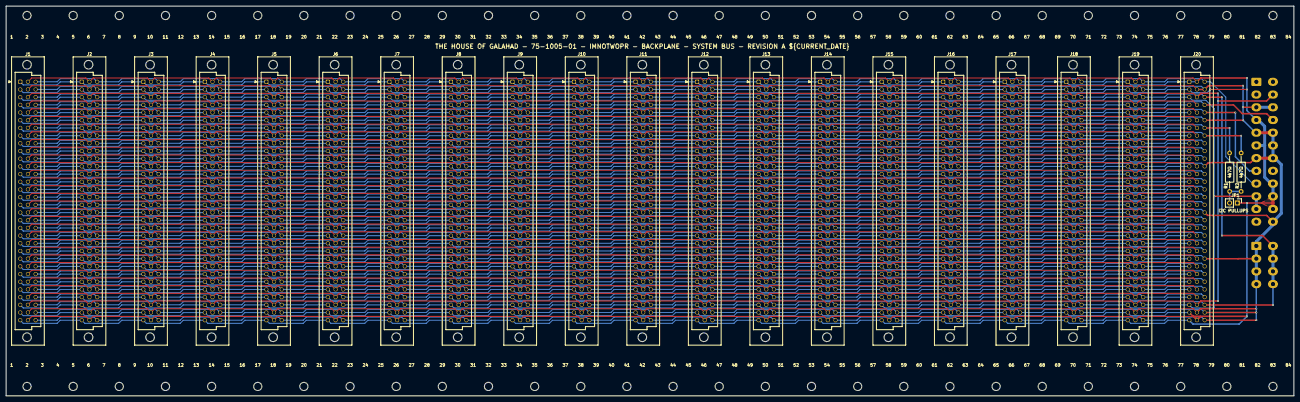
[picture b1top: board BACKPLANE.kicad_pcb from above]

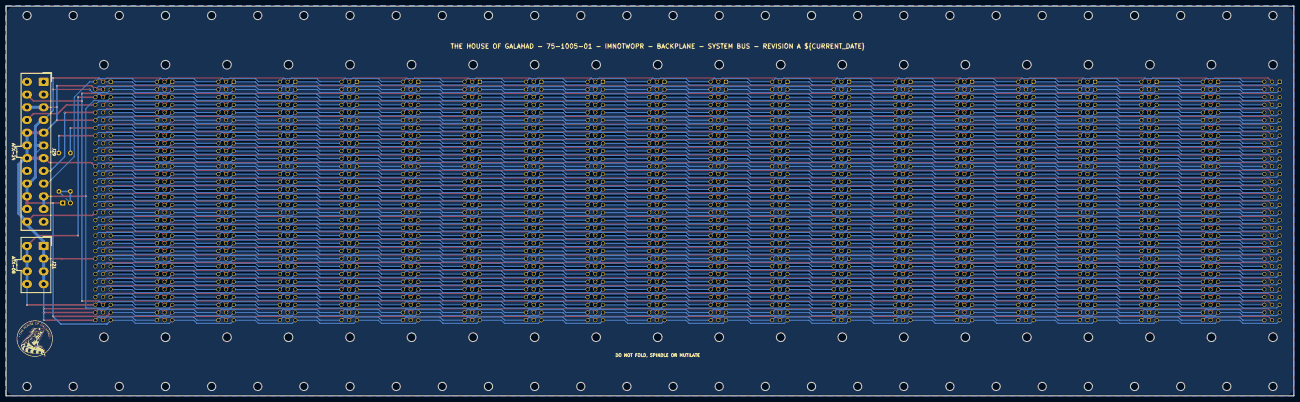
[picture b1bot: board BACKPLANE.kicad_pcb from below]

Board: 2 copper layers, 425.3 x 128.7 mm, 81 parts (2 on the bottom side), 81 nets.

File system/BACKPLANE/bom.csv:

"Reference","Qty","Value","DNP","Exclude from BOM","Exclude from Board","Footprint","Datasheet"
"J1,J2,J3,J4,J5,J6,J7,J8,J9,J10,J11,J12,J13,J14,J15,J16,J17,J18,J19,J20","20","BusConnector","","","","IMNOTWOPR:SystemConnector_Female",""
"J21","1","ATX-08","","","","IMNOTWOPR:ATX-08",""
"J29","1","ATX-24","","","","IMNOTWOPR:ATX-24","https://www.intel.com/content/dam/www/public/us/en/documents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"
"JP1","1","I2C PULLUPS","","","","FormantKO:Jumper_1x02",""
"R1,R2","2","4k7Ω","","","","IMNOTWOPR:R_Axial_DIN0207_P400mil",""
